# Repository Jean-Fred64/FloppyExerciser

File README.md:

# :floppy_disk: Floppy Drive Exerciser

# Version : GPS 🇯🇵 # Mr JeAn-FReD 🇫🇷

This board helps test floppy drives of several different types:

* Standard IBM 34-pin drives (3.5" and 5.25")
* IBM PS/2 40-pin drives with embedded power connections
* Shugart 8" floppy drives
* Apple II (original Disk II)
* HP 34-pin drives (as found in many 9122 enclosures)
* HP 26-pin drives (found in older enclosures and machines)
* IBM 31SD and 51TD floppy drives
* Shugart 3.5" (Commodore Amiga) floppy drives with [50 pin to 34 pin adapter](https://github.com/Jean-Fred64/FloppyExerciser/blob/Jean_Fred64/50%20pin%20to%2034%20pin%20Mr%20JEANxFRED/readme.md#50-pin-to-34-pin-adapter-for-floppy-drive-exerciser)

The board basically breaks out every signal to a control switch, indicator LED, or test point. It's not designed as a flux imaging tool--it's just a simple way to exercise features of a floppy drive.

There is an optional section of the board that is a step controller for the head stepper motor. This controller has an encoder wheel and a small 7-segment display. It will let you select and automatically step to a particular track.

Features include:

* Two potentiometers control step pulse width and step period (speed)
* Generates TG43 signal (Track greater than 43, for variable write current)
* Alignment mode makes it easy to cycle between track 0, middle, and last track
* Supports half tracking (Apple II) and double tracking modes
* Supports direct stepper motor drive through separate header
* Direct stepper drive supports half track, double track, and 1.5x tracking, useful for getting 32 tpi from a 48tpi drive
* Auto track 0 seek function will try to locate track 0

The fab files are [here](https://github.com/Jean-Fred64/FloppyExerciser/tree/Jean_Fred64/Prod).

The schematic is [here](https://github.com/Jean-Fred64/FloppyExerciser/blob/Jean_Fred64/KiCad/FloppyExerciser.pdf).

The bill of materials is [here](https://github.com/Jean-Fred64/FloppyExerciser/blob/Jean_Fred64/BOM)

## Fabrication notes

The board is 100mm x 100mm, 2 layer, standard 1.6mm thickness.

Use toggle switches, not slide switches, otherwise the silkscreen markings will be reveresed.

Use a 3-position switch for the TG43 switch.

Use SIP sockets for RN1 and RN2 so you can swap in different termination resistor values. I usually use 1K.

Be careful about putting any signals on `J2`. If `EN WRITE` gets grounded (the adjacent pin is ground) then it will enable writes on any connected drive, erasing the existing track.

## Connecting Drives

* **Apple II**: Use connector `J12`. Apply -12V, +5V, and +12V to the test points on the left side of the board.
* **PC**: Use connector `J6`. Apply +5V to the test point on the left side of the board. Connect a Molex connector to the floppy drive for power (+5V and sometimes +12V).
* **PS/2**: Use connector `J11`. Apply +5V and +12V to the test points on the left side of the board.
* **Shugart**: Use connector `J9`. Apply +5V to the test point on the left side of the board. Connect the drive to power externally (typically +5V, +24V, and 120VAC).
* **IBM 31SD/51TD**: Use connector `J10`. The 31SD has fewer pins, line it up with pin 1. Apply +5V, -5V, and +24V to the test points on the left side of the board.
* **HP 34-pin**: Use connector `J7`. Apply +5V and +12V to the test points on the left side of the board.
* **HP 26-pin**: Use connector `J8`. Apply +5V to the board and external power to the HP drive.

The board can directly drive an external 4-phase stepper motor. Attach the stepper motor to `J1` and connect either +12V or +24V power to the test points on the left side, and set jumper `J4` to pick the voltage.

## Firmware

### Building the Firmware

The code for the ATMega328PB microcontroller is meant to run without a bootloader and can be built from the command line if you
have installed `avr-gcc` and `avrdude`.

```
make
make fuses
make prog
```

Note that the avrdude command lines in the makefile are hard-coded for the usbtiny programmer. You'll want to change that if you have another type of AVR programmer.

The MCU is new enough that your version of avr-gcc and avrdude may not
support it yet, see [here](https://gist.github.com/goncalor/51e1c8038cc058b4379552477255b4e1) for instructions on how to fix that.

The bottom of the board has a standard 6-pin AVR programming header as a surface mount footprint. Since you only need to program it once, you could plug a header into the programmer's cable and physically push it up against the board, or you could temporarily tack-solder it in place. Or just leave it soldered in place and install standoffs in the corners of the board.

### Using the Firmware

On startup, the display will temporarily indicate `HI` and then prompt you for the stepping mode:

* `SS` - single step
* `DS` - double step
* `HS` - half step
* `15` - 1.5x step

Half step mode and 1.5x step are supported on the direct drive stepper motor header and the Apple II header.

Select the mode with the encoder wheel and then push it down to select the option.

The display now indicates the current track. Move the encoder wheel to pick a new track. The display will blink to indicate your desired track. Once you are satisfied with it, push down on the encoder to select that track.

*Tips :*
if you push and hold the button down while turning it, it immediately steps to that track while displaying that track number

For additional functions, you can push the menu button. Menu options are selected with the encoder wheel:

* `HO` - Home to track 0. The controller seeks until TRACK0 asserts or it steps by 80 tracks
* `A8` - Alignment mode for 80 tracks. In this mode, the encoder switches between track 0, track 39, and track 79
* `A7` - Alignment mode for 77 tracks
* `A4` - Alignment mode for 40 tracks
* `35` - Alignment mode for 35 tracks

To exit alignment modes, push the menu button.

The board will control the TG43 (track greater than 43) signal used by 8" drives as long as the switch is set to "AUTO".

* **RATE (RV1)** - rate sets how fast the firmware steps the drive

* **Pulse width (RV2)** - pulse width sets how wide the pulses are that it feeds to the drive, sometimes you have to adjust it for certain drives.

* **STEP (SW2)** - STEP lets you manually step the stepper motor even with no firmware.

* **DIR OUT / AUTO - IN (SW10)** - DIR OUT means step the head to the outside edge direction - AUTO means let the firmware control the direction pin - DIR IN means step in towards the hub.

* **DISKCHG RESET (HP) (SW3)** - DISKCHG RESET is only for certain HP drives that have a flip flop built in for tracking disk changes.

## Licensing

This work is licensed under a Creative Commons Attribution-ShareAlike 4.0 International License. See [https://creativecommons.org/licenses/by-sa/4.0/](https://creativecommons.org/licenses/by-sa/4.0/).

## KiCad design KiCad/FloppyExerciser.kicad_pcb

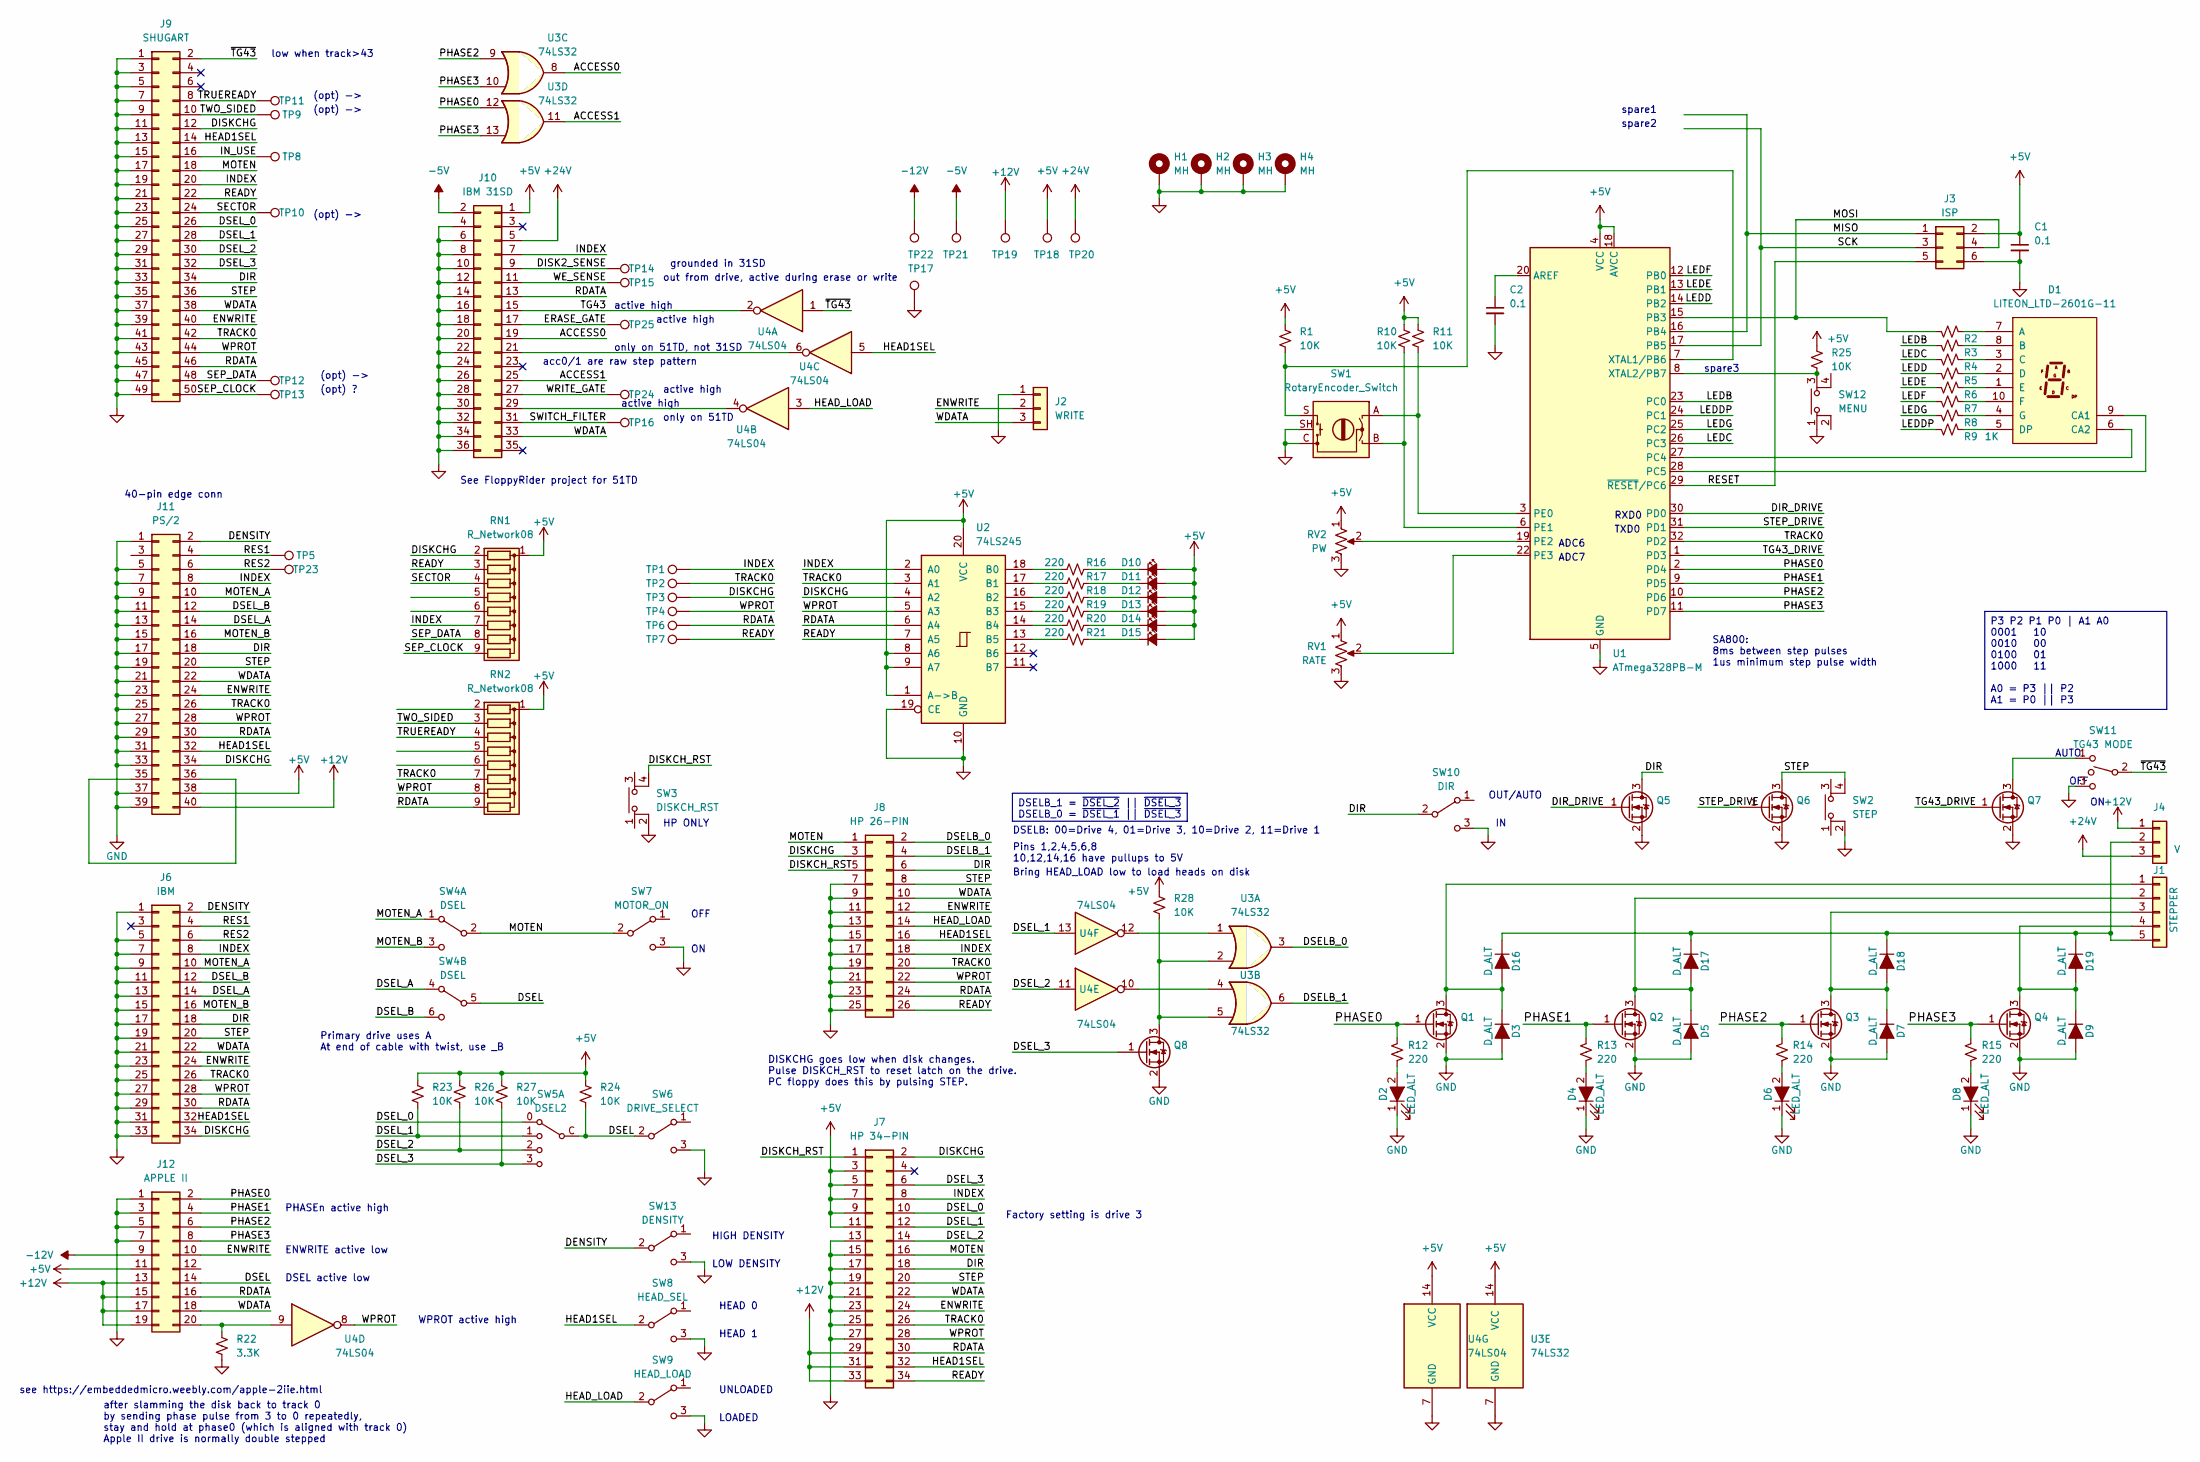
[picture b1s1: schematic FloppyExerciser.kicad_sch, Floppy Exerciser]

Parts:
C1, C2: 0.1; CAPC1608X100; Digikey 399-C0603C104K4RAC7867CT-ND
D1: LITEON_LTD-2601G-11; LTD-2601G-11; Digikey 160-1922-5-ND
D2, D4, D6, D8: LED_ALT; LEDM1608X50; Digikey 160-1445-1-ND
D3, D5, D7, D9, D16, D17, D18, D19: D_ALT; DIOM5226X210; Digikey ES1B-E3/61TGICT-ND
D10, D11, D12, D13, D14, D15: LED_Small_Filled; LEDM1608X50; Digikey 160-1445-1-ND
H1, H2, H3, H4: MH; MH_125_200
J1: STEPPER; PinHeader_1x05_P2.54mm_Vertical
J2: WRITE; PinHeader_1x03_P2.54mm_Vertical
J3: ISP; PinHeader_2x03_P2.54mm_Vertical_SMD
J4: V; PinHeader_1x03_P2.54mm_Vertical
J6: IBM; PinHeader_2x17_P2.54mm_Vertical
J7: HP 34-PIN; PinHeader_2x17_P2.54mm_Vertical
J8: HP 26-PIN; PinHeader_2x13_P2.54mm_Vertical
J9: SHUGART; PinHeader_2x25_P2.54mm_Vertical
J10: IBM 31SD; PinHeader_2x18_P2.54mm_Vertical
J11: PS/2; EDAC_395-040-559-212; Mouser 587-395-040-558-201
J12: APPLE II; PinHeader_2x10_P2.54mm_Vertical
Q1, Q2, Q3, Q4, Q5, Q6, Q7, Q8: N-Channel 40 V 4.3A (Ta), 5.6A (Tc) 1.25W (Ta), 2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; SOT95P230X117-3; Mouser 78-SI2318CDS-T1-BE3
R1, R10, R11, R23, R24, R25, R26, R27, R28: 10K; RESC1608X55; Digikey 541-2204-1-ND
R2, R3, R4, R5, R6, R7, R8, R9: 1K; RESC1608X55; Digikey 541-1.00KHCT-ND
R12, R13, R14, R15, R16, R17, R18, R19, R20, R21: 220; RESC1608X55; Digikey 541-220HCT-ND
R22: 3.3K; RESC1608X55; Digikey 541-3.30KHCT-ND
RN1, RN2: R_Network08; R_Array_SIP9; Digikey 4609X-101-102LF-ND
RV1: RATE; BOURNS_3386_VERT_UNIVERSAL; Digikey 3386F-1-202TLF
RV2: PW; BOURNS_3386_VERT_UNIVERSAL; Digikey 3386F-1-202TLF
SW1: RotaryEncoder_Switch; PANASONIC_EVEY; Mouser 667-EVE-YBCAJO16B
SW2: STEP; ESWITCH_TL1105; Digikey EG1828-ND
SW3: DISKCH_RST; ESWITCH_TL1105; Digikey EG1828-ND
SW4: DSEL; SW_DPDT; Digikey 100DP1T1B1M2QE
SW5: DSEL2; CTS_220AD_04; Digikey CT3098-ND
SW6: DRIVE_SELECT; SW_SPDT; Mouser 612-100-A1421
SW7: MOTOR_ON; SW_SPDT; Mouser 612-100-A1421
SW8: HEAD_SEL; SW_SPDT; Mouser 612-100-A1421
SW9: HEAD_LOAD; SW_SPDT; Mouser 612-100-A1421
SW10: DIR; SW_SPDT; Mouser 612-100-A1421
SW11: TG43 MODE; SW_SPDT; Digikey 141-100DP6T3B4M2QE-ND
SW12: MENU; ESWITCH_TL1105; Digikey EG1828-ND
SW13: DENSITY; SW_SPDT; Mouser 612-100-A1421
TP1, TP2, TP3, TP4, TP5, TP6, TP7, TP8, TP9, TP10, TP11, TP12, TP13, TP14, TP15, TP16, TP17, TP18, TP19, TP20, TP21, TP22, TP23, TP24, TP25: TestPoint; TP_KEYSTONE_5005_9; Digikey 36-5006-ND
U1: ATmega328PB-M; QFN-32-1EP_5x5mm_P0.5mm_EP3.1x3.1mm; Digikey ATMEGA328PB-MU-ND
U2: 74LS245; SOP127P1065X265-20; Mouser 595-SN74LS245DW
U3: 74LS32; SOP127P620X175-14; Mouser 595-SN74LS32DR
U4: 74LS04; SOP127P620X175-14; Mouser 595-SN74LS04D

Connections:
+5V: C1.1, D10.2 (A), D11.2 (A), D12.2 (A), D13.2 (A), D14.2 (A), D15.2 (A), J3.2, J7.3, J7.5, J7.7, J7.9, J7.11, J10.1, J11.38, J12.11, R1.1, R10.1, R11.1, R23.1, R24.1, R25.1, R26.1, R27.1, R28.1, RN1.1 (common), RN2.1 (common), RV1.1, RV2.1, TP18.1, U1.4 (VCC), U1.18 (AVCC), U2.1 (A->B), U2.8 (A6), U2.9 (A7), U2.20 (VCC), U3.14 (VCC), U4.14 (VCC)
+12V: J4.1, J7.29, J7.31, J7.33, J11.40, J12.13, J12.15, J12.17, J12.19, TP19.1
+24V: J4.3, J10.5, TP20.1
-5V: J10.2, TP21.1
-12V: J12.9, TP22.1
/ACCESS0: J10.19, U3.8
/ACCESS1: J10.25, U3.11
/DENSITY: J6.2, J11.2, SW13.2 (B)
/DIR: J6.18, J7.18, J8.6, J9.34, J11.18, Q5.3 (D), SW10.2 (B)
/DIR_DRIVE: Q5.1 (G), U1.30 (PD0)
/DISK2_SENSE: J10.9, TP14.1
/DISKCHG: J6.34, J7.2, J8.3, J9.12, J11.34, RN1.2 (R1), TP3.1, U2.4 (A2)
/DISKCH_RST: J7.1, J8.5, SW3.4
/DSEL: J12.14, R24.2, SW4.5 (B), SW5.C, SW6.2 (B)
/DSELB_0: J8.2, U3.3
/DSELB_1: J8.4, U3.6
/DSEL_0: J7.10, J9.26, SW5.0
/DSEL_1: J7.12, J9.28, R23.2, SW5.1, U4.13
/DSEL_2: J7.14, J9.30, R26.2, SW5.2, U4.11
/DSEL_3: J7.6, J9.32, Q8.1 (G), R27.2, SW5.3
/DSEL_A: J6.14, J11.14, SW4.4 (A)
/DSEL_B: J6.12, J11.12, SW4.6 (C)
/ENWRITE: J2.2, J6.24, J7.24, J8.12, J9.40, J11.24, J12.10
/ERASE_GATE: J10.17, TP25.1
/HEAD1SEL: J6.32, J7.32, J8.16, J9.14, J11.32, SW8.2 (B), U4.5
/HEAD_LOAD: J8.14, SW9.2 (B), U4.3
/INDEX: J6.8, J7.8, J8.18, J9.20, J10.7, J11.8, RN1.7 (R6), TP1.1, U2.2 (A0)
/IN_USE: J9.16, TP8.1
/LEDB: R3.1, U1.23 (PC0)
/LEDC: R4.1, U1.26 (PC3)
/LEDD: R5.1, U1.14 (PB2)
/LEDDP: R9.1, U1.24 (PC1)
/LEDE: R6.1, U1.13 (PB1)
/LEDF: R7.1, U1.12 (PB0)
/LEDG: R8.1, U1.25 (PC2)
/MISO: J3.1, U1.16 (PB4)
/MOSI: J3.4, R2.1, U1.15 (PB3)
/MOTEN: J7.16, J8.1, J9.18, SW4.2 (B), SW7.2 (B)
/MOTEN_A: J6.10, J11.10, SW4.1 (A)
/MOTEN_B: J6.16, J11.16, SW4.3 (C)
/PHASE0: J12.2, Q1.1 (G), R12.2, U1.2 (PD4), U3.12
/PHASE1: J12.4, Q2.1 (G), R13.2, U1.9 (PD5)
/PHASE2: J12.6, Q3.1 (G), R14.2, U1.10 (PD6), U3.9
/PHASE3: J12.8, Q4.1 (G), R15.2, U1.11 (PD7), U3.10, U3.13
/RDATA: J6.30, J7.30, J8.24, J9.46, J10.13, J11.30, J12.16, RN2.9 (R8), TP6.1, U2.6 (A4)
/READY: J7.34, J8.26, J9.22, RN1.3 (R2), TP7.1, U2.7 (A5)
/RES1: J6.4, J11.4, TP5.1
/RES2: J6.6, J11.6, TP23.1
/RESET: J3.5, U1.29 (~RESET/PC6)
/SCK: J3.3, U1.17 (PB5)
/SECTOR: J9.24, RN1.4 (R3), TP10.1
/SEP_CLOCK: J9.50, RN1.9 (R8), TP13.1
/SEP_DATA: J9.48, RN1.8 (R7), TP12.1
/STEP: J6.20, J7.20, J8.8, J9.36, J11.20, Q6.3 (D), SW2.4
/STEP_DRIVE: Q6.1 (G), U1.31 (PD1)
/SWITCH_FILTER: J10.31, TP16.1
/TG43: J10.15, U4.2
/TG43_DRIVE: Q7.1 (G), U1.1 (PD3)
/TRACK0: J6.26, J7.26, J8.20, J9.42, J11.26, RN2.7 (R6), TP2.1, U1.32 (PD2), U2.3 (A1)
/TRUEREADY: J9.8, RN2.4 (R3), TP11.1
/TWO_SIDED: J9.10, RN2.3 (R2), TP9.1
/WDATA: J2.3, J6.22, J7.22, J8.10, J9.38, J10.33, J11.22, J12.18
/WE_SENSE: J10.11, TP15.1
/WPROT: J6.28, J7.28, J8.22, J9.44, J11.28, RN2.8 (R7), TP4.1, U2.5 (A3), U4.8
/WRITE_GATE: J10.27, TP24.1
/~TG43: J9.2, SW11.2, U4.1
GND: C1.2, C2.2, D2.1 (K), D3.2 (A), D4.1 (K), D5.2 (A), D6.1 (K), D7.2 (A), D8.1 (K), D9.2 (A), H1.1, H2.1, H3.1, H4.1, J2.1, J3.6, J6.1, J6.5, J6.7, J6.9, J6.11, J6.13, J6.15, J6.17, J6.19, J6.21, J6.23, J6.25, J6.27, J6.29, J6.31, J6.33, J7.13, J7.15, J7.17, J7.19, J7.21, J7.23, J7.25, J7.27, J8.7, J8.9, J8.11, J8.13, J8.15, J8.17, J8.19, J8.21, J8.23, J8.25, J9.1, J9.3, J9.5, J9.7, J9.9, J9.11, J9.13, J9.15, J9.17, J9.19, J9.21, J9.23, J9.25, J9.27, J9.29, J9.31, J9.33, J9.35, J9.37, J9.39, J9.41, J9.43, J9.45, J9.47, J9.49, J10.4, J10.6, J10.8, J10.10, J10.12, J10.14, J10.16, J10.18, J10.20, J10.22, J10.24, J10.26, J10.28, J10.30, J10.32, J10.34, J10.36, J11.1, J11.5, J11.7, J11.9, J11.11, J11.13, J11.15, J11.17, J11.19, J11.21, J11.23, J11.25, J11.27, J11.29, J11.31, J11.33, J11.37, J11.39, J12.1, J12.3, J12.5, J12.7, Q1.2 (S), Q2.2 (S), Q3.2 (S), Q4.2 (S), Q5.2 (S), Q6.2 (S), Q7.2 (S), Q8.2 (S), R22.2, RV1.3, RV2.3, SW1.C, SW1.SH, SW2.2, SW3.2, SW6.3 (C), SW7.3 (C), SW8.3 (C), SW9.3 (C), SW10.3 (C), SW11.3, SW12.1, SW13.3 (C), TP17.1, U1.5 (GND), U1.21 (GND), U1.33 (GND), U2.10 (GND), U2.19 (CE), U3.7 (GND), U4.7 (GND)
unnamed: D1.7 (A), R2.2
unnamed: D1.8 (B), R3.2
unnamed: D1.3 (C), R4.2
unnamed: D1.9 (CA1), U1.28 (PC5)
unnamed: D1.6 (CA2), U1.27 (PC4)
unnamed: D1.2 (D), R5.2
unnamed: D1.5 (DP), R9.2
unnamed: D1.1 (E), R6.2
unnamed: D1.10 (F), R7.2
unnamed: D1.4 (G), R8.2
unnamed: D2.2 (A), R12.1
unnamed: D4.2 (A), R13.1
unnamed: D6.2 (A), R14.1
unnamed: D8.2 (A), R15.1
unnamed: D10.1 (K), R16.2
unnamed: D11.1 (K), R17.2
unnamed: D12.1 (K), R18.2
unnamed: D13.1 (K), R19.2
unnamed: D14.1 (K), R20.2
unnamed: D15.1 (K), R21.2
unnamed: D3.1 (K), D16.2 (A), J1.1, Q1.3 (D)
unnamed: D16.1 (K), D17.1 (K), D18.1 (K), D19.1 (K), J1.5, J4.2
unnamed: D5.1 (K), D17.2 (A), J1.2, Q2.3 (D)
unnamed: D7.1 (K), D18.2 (A), J1.3, Q3.3 (D)
unnamed: D9.1 (K), D19.2 (A), J1.4, Q4.3 (D)
unnamed: J10.21, U4.6
unnamed: J10.29, U4.4
unnamed: J11.35, J11.36
unnamed: J12.20, R22.1, U4.9
unnamed: Q7.3 (D), SW11.1
unnamed: Q8.3 (D), R28.2, U3.2, U3.5
unnamed: C2.1, U1.20 (AREF)
unnamed: R11.2, SW1.A, U1.3 (PE0)
unnamed: R10.2, SW1.B, U1.6 (PE1)
unnamed: RV2.2, U1.19 (PE2)
unnamed: RV1.2, U1.22 (PE3)
unnamed: R1.2, SW1.S, U1.7 (XTAL1/PB6)
unnamed: R25.2, SW12.3, U1.8 (XTAL2/PB7)
unnamed: R16.1, U2.18 (B0)
unnamed: R17.1, U2.17 (B1)
unnamed: R18.1, U2.16 (B2)
unnamed: R19.1, U2.15 (B3)
unnamed: R20.1, U2.14 (B4)
unnamed: R21.1, U2.13 (B5)
unnamed: U3.1, U4.12
unnamed: U3.4, U4.10

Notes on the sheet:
WPROT active high
low when track>43
OUT/AUTO
active high
DISKCHG goes low when disk changes. Pulse DISKCH_RST to reset latch on the drive. PC floppy does this by pulsing STEP.
(opt) ->
ENWRITE active low
DSELB: 00=Drive 4, 01=Drive 3, 10=Drive 2, 11=Drive 1
spare3
AUTO
OFF
PHASEn active high
out from drive, active during erase or write
HIGH DENSITY
Factory setting is drive 3
LOADED
grounded in 31SD
Primary drive uses A At end of cable with twist, use _B
See FloppyRider project for 51TD
after slamming the disk back to track 0 by sending phase pulse from 3 to 0 repeatedly, stay and hold at phase0 (which is aligned with track 0) Apple II drive is normally double stepped
TXD0
HEAD 0
Pins 1,2,4,5,6,8 10,12,14,16 have pullups to 5V
HP ONLY
(opt) ?
spare2
UNLOADED
only on 51TD, not 31SD
ADC7
HEAD 1
ADC6
Bring HEAD_LOAD low to load heads on disk
DSEL active low
see https://embeddedmicro.weebly.com/apple-2iie.html
RXD0
acc0/1 are raw step pattern
spare1
LOW DENSITY
SA800: 8ms between step pulses 1us minimum step pulse width
only on 51TD

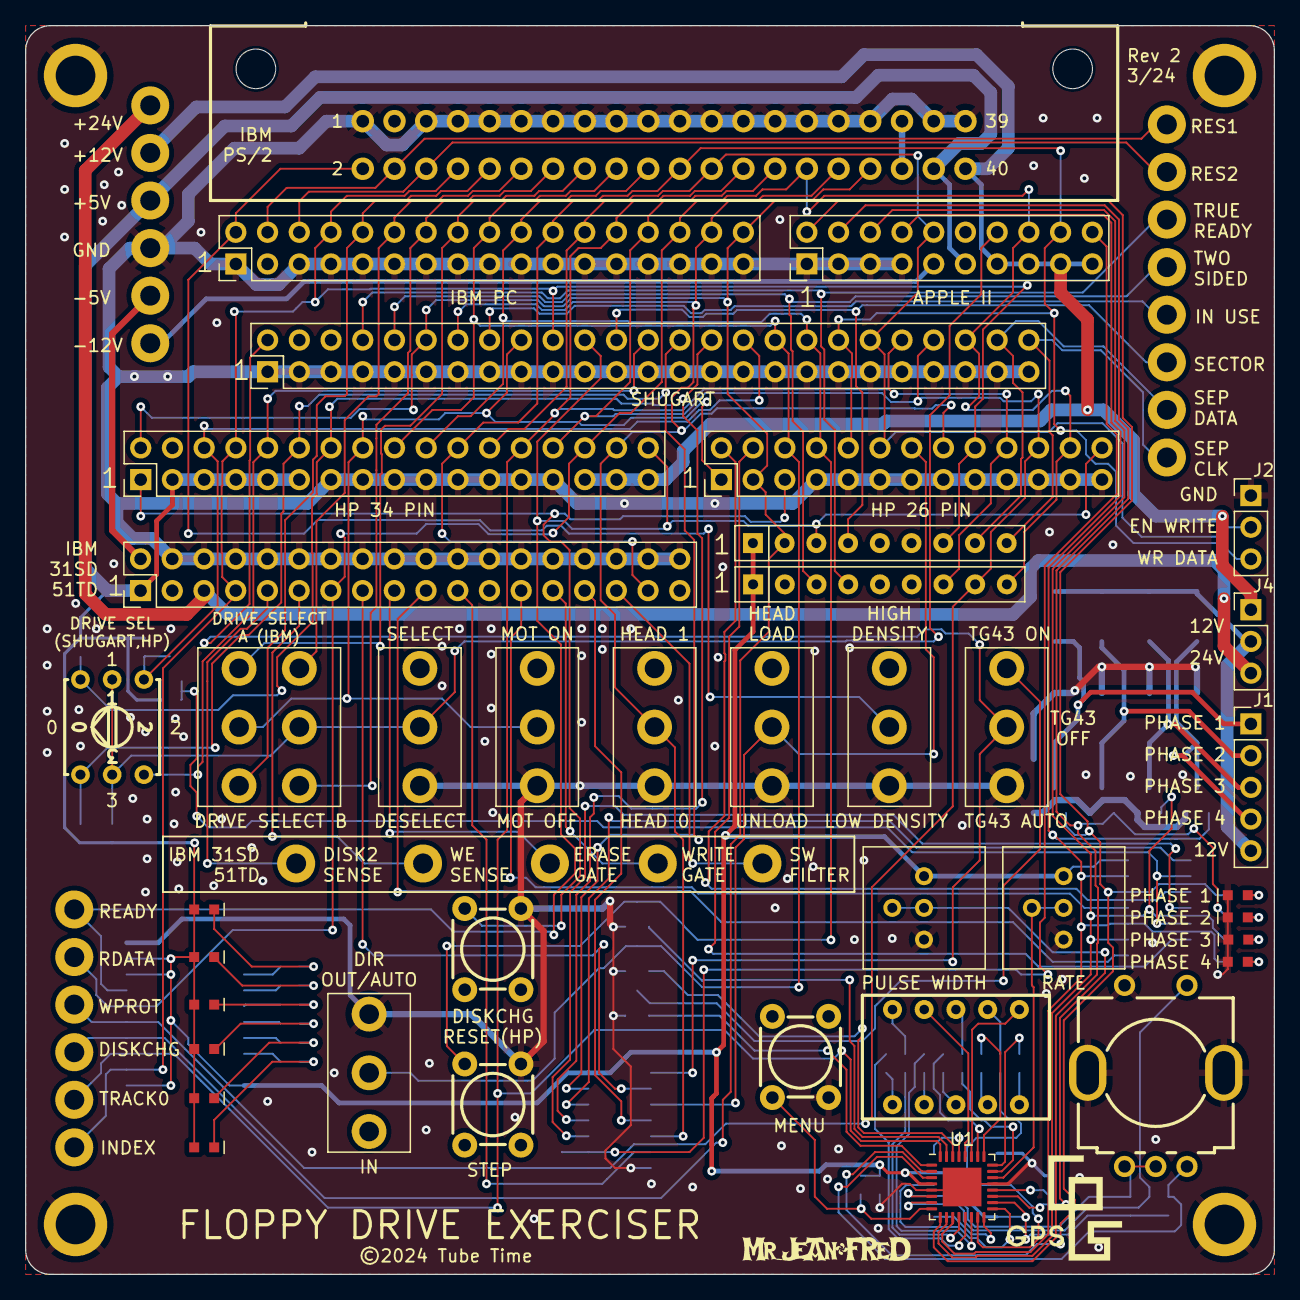
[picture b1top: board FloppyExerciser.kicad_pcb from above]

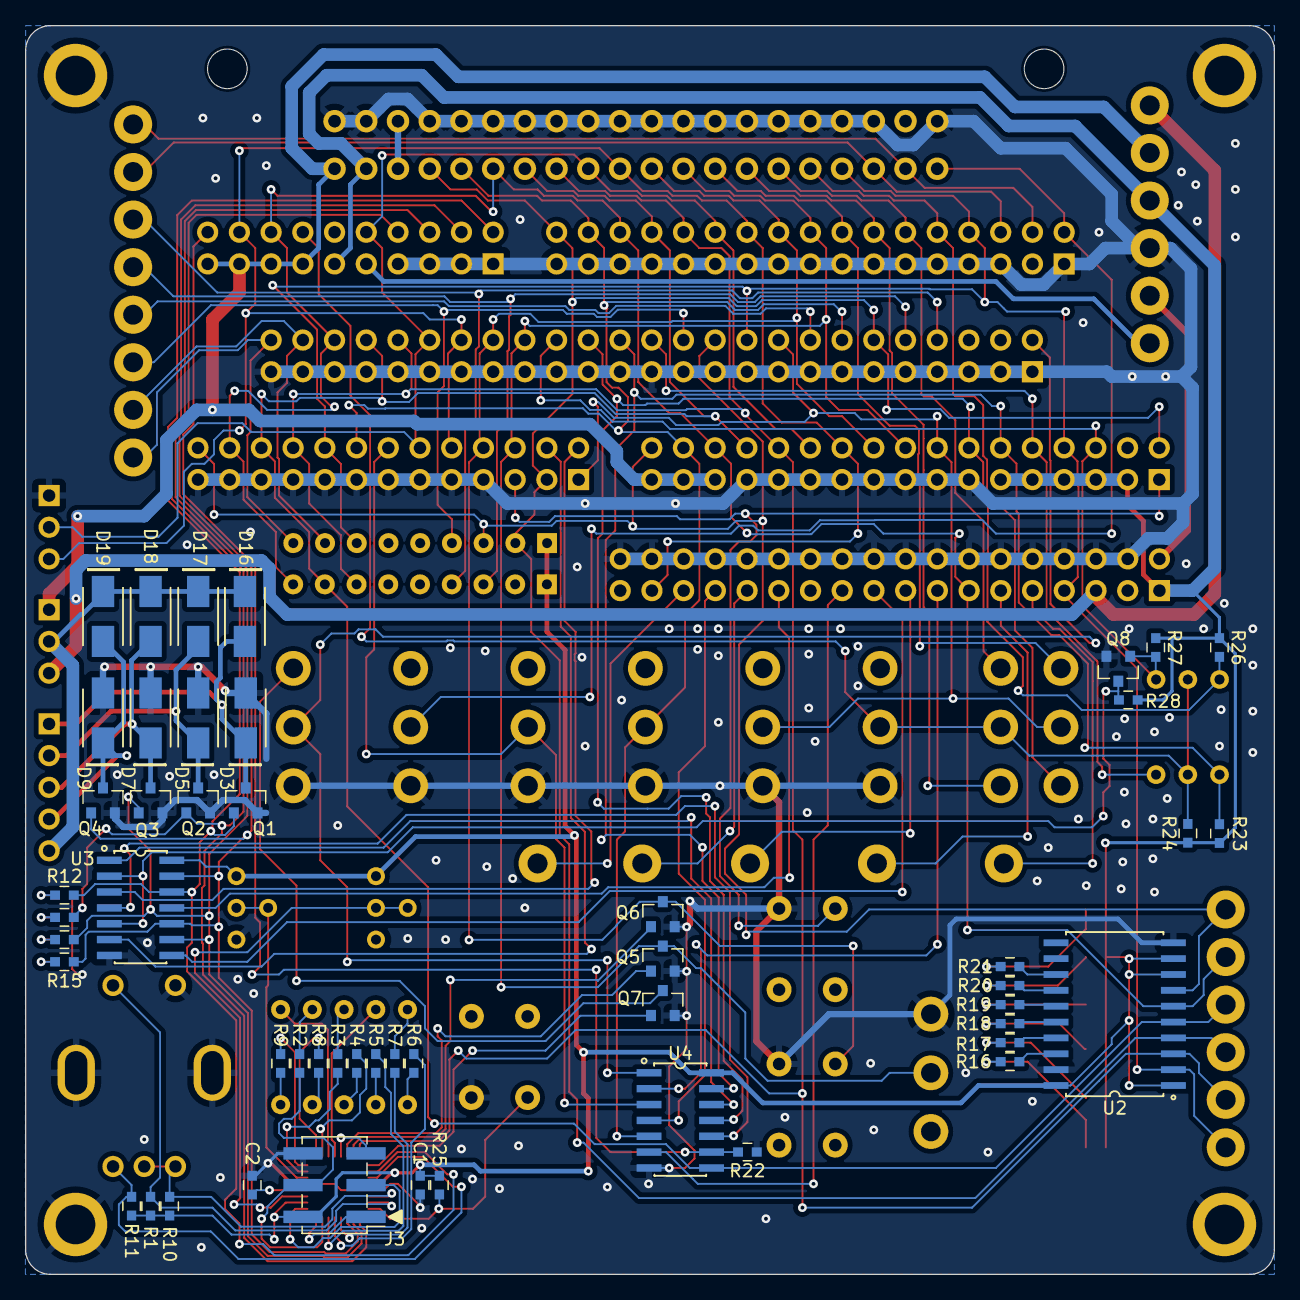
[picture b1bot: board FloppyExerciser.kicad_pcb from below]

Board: 2 copper layers, 100.0 x 100.0 mm, 118 parts (50 on the bottom side), 113 nets.

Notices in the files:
KiCad/FloppyExerciser.kicad_pcb:
©2024 Tube Time
